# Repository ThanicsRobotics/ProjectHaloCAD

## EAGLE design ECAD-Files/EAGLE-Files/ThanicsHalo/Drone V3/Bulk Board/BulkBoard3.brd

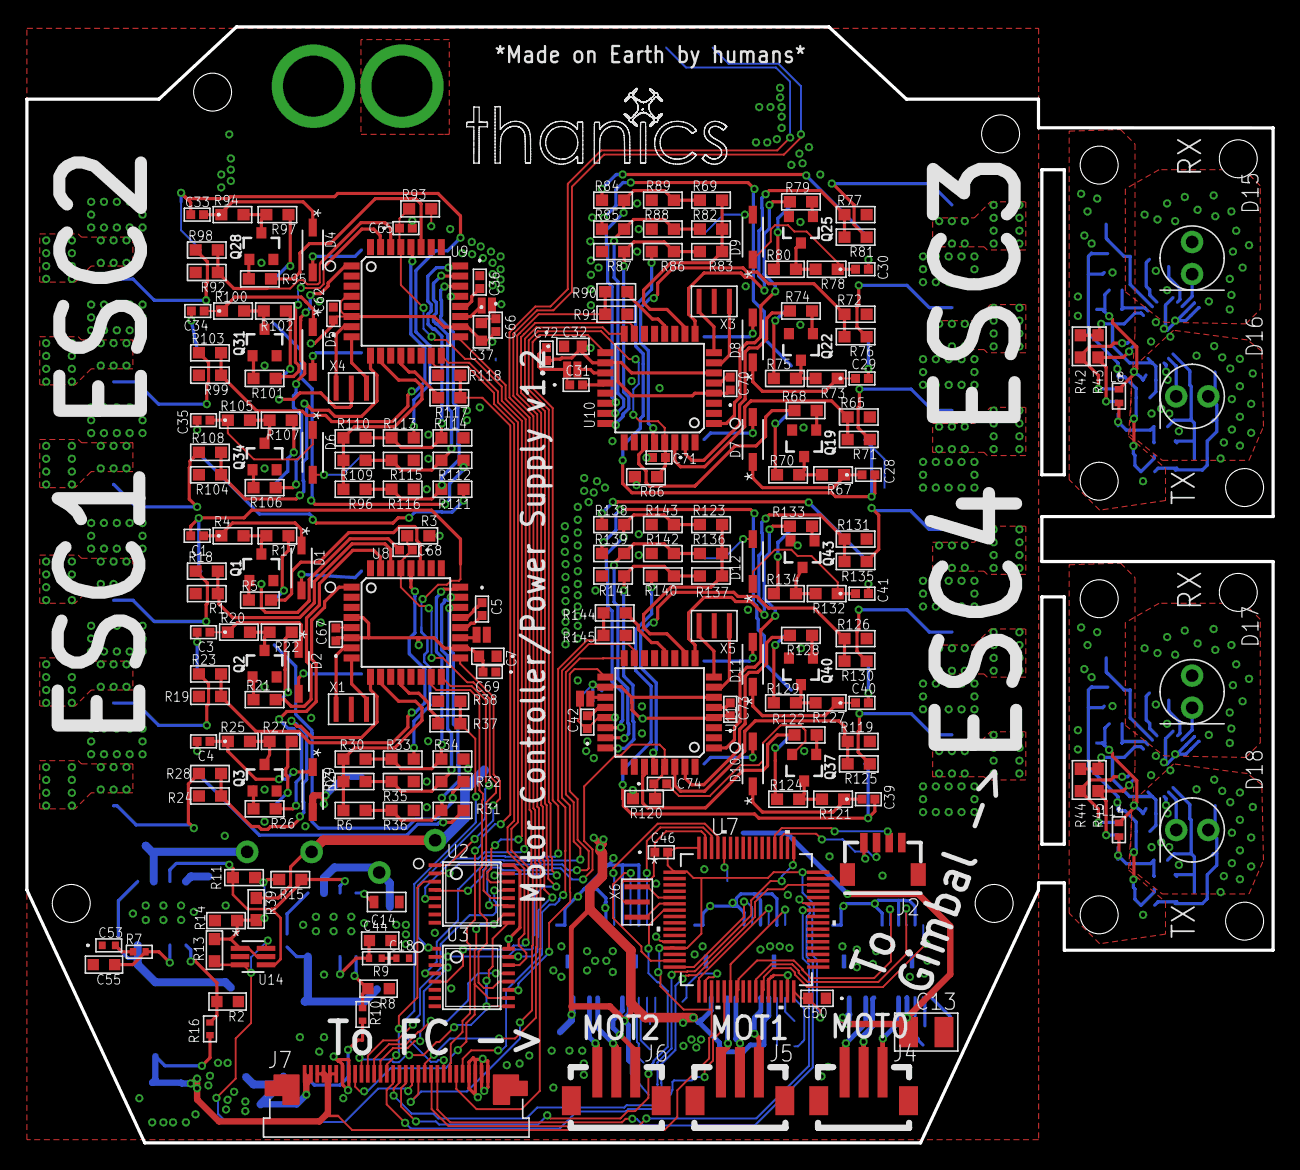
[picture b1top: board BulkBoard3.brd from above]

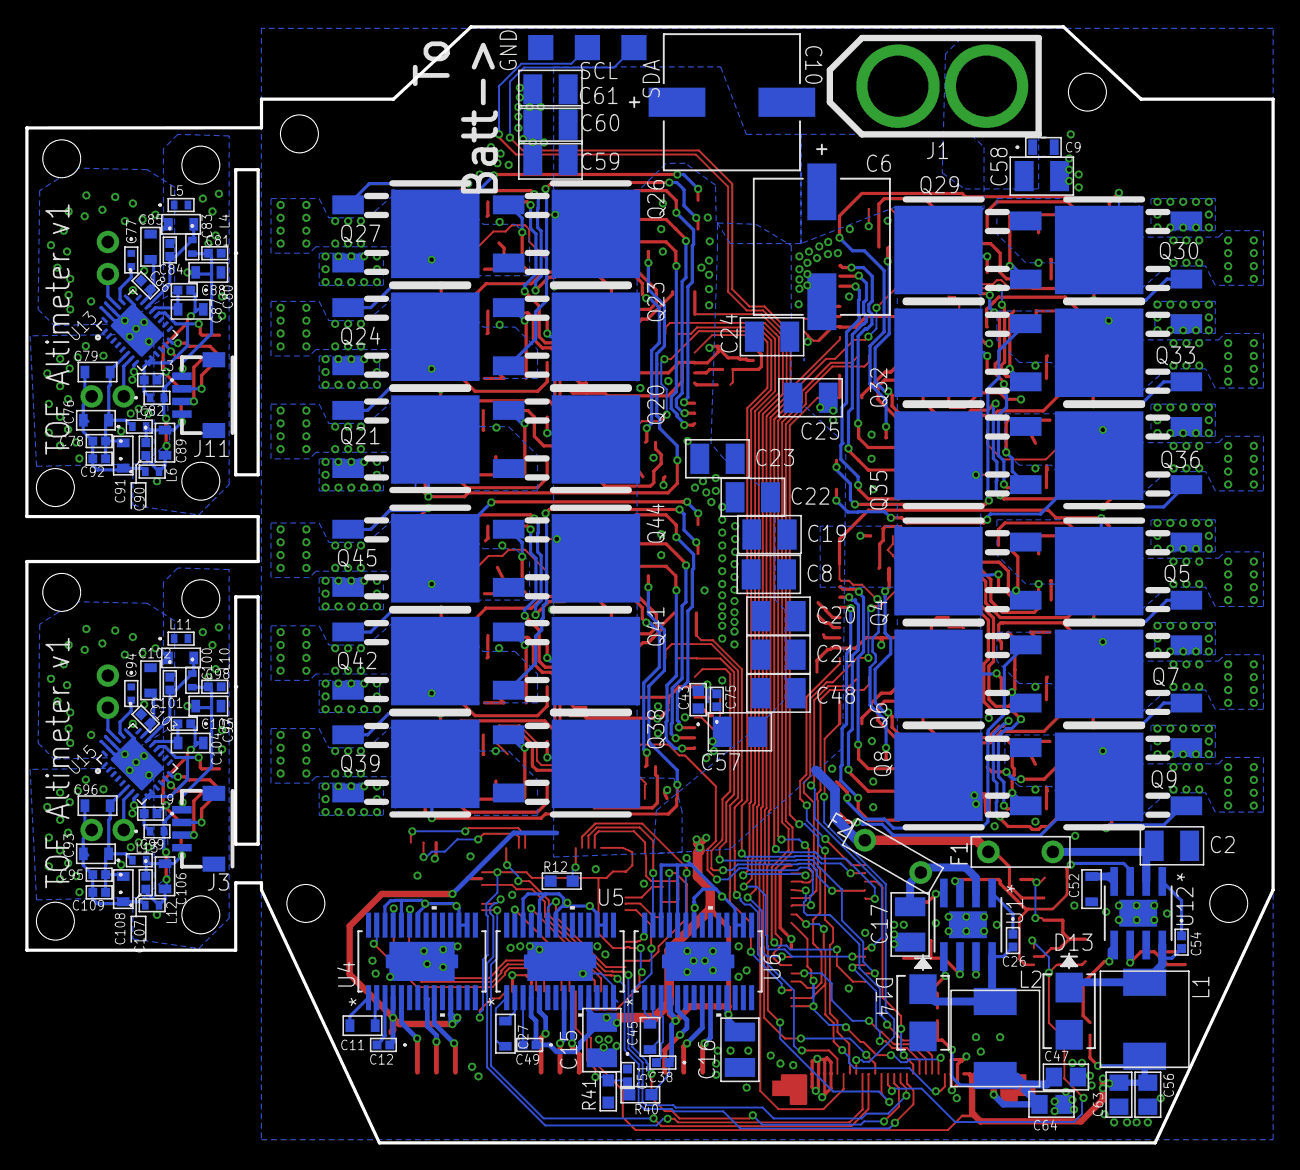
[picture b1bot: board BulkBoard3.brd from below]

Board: 4 copper layers, 98.6 x 88.3 mm, 340 parts (127 on the bottom side), 249 nets.

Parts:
C1, C3, C4, C28, C29, C30, C33, C34, C35, C39, C40, C41: 0.1uF (50V); 0402-M
C2, C8, C13, C15, C16, C17, C19, C20, C21, C22, C23, C24, C25, C48, C57, C58, C59, C60, C61: 22uF; 1210_CAPACITOR
C5, C12, C26, C31, C36, C38, C42, C46, C49, C51, C54, C62, C65, C66, C67, C68, C69, C70, C71, C72, C73, C74, C75, C78, C81, C82, C84, C86, C88, C90, C92, C95, C98, C99, C101, C103, C105, C107, C109: 0.1uF; 0402-M
C6, C10: 470uF; PCAP_10X10-ELECT-M
C7, C32, C37, C43, C50: 2.2uF; G-188-M
C9: 10uF; G-21
C11, C14, C27, C45, C52: 10nF; 0603_CAPACITOR
C18: 1nF; C0402
C44, C55: 43pF; C0603
C47, C56, C63, C64: 22uF; C0805
C53: 2.2nF; 0402_CAPACITOR
C76, C79, C80, C83, C85, C87, C89, C91, C93, C96, C97, C100, C102, C104, C106, C108: 1uF; 0603_CAPACITOR
C77, C94: 6pF; 0402_CAPACITOR
D1, D2, D3, D4, D5, D6, D7, D8, D9, D10, D11, D12: 1N4148; SOD123-M
D13, D14: SSB44-E3/52T; DIODE_DO214AA_MBRS-M
D15, D17: SFH203FA; 5MM_LED
D16, D18: SFH4550; 5MM_LED
F1, F2: 0ZRB0400FF1A
GND: TPTP20SQ; TP20SQ
J1: ESC_CONTACTS; XT60_CONNECTOR
J2, J3, J11: JST_SH_4POS
J4, J5, J6: B3B-ZR-SM4
J7: SFV30R-1STE1HLF
JP1, JP3, JP4, JP5: JUMPER-SMT_2_NO_NO-SILK; SMT-JUMPER_2_NO_NO-SILK
L1, L2: 10uH; PA431.XXX
L3, L4, L5, L6, L7, L8, L9, L10, L11, L12, L13, L14: MMZ1005S182ET000IND_1005-M; IND_1005-M
Q1, Q2, Q3, Q19, Q22, Q25, Q28, Q31, Q34, Q37, Q40, Q43: 500mA/300V; SOT23-3
Q4, Q5, Q6, Q7, Q8, Q9, Q20, Q21, Q23, Q24, Q26, Q27, Q29, Q30, Q32, Q33, Q35, Q36, Q38, Q39, Q41, Q42, Q44, Q45: IRLR8726; DPAK
R1, R3, R12, R19, R24, R37, R38, R40, R65, R66, R72, R77, R90, R91, R92, R93, R99, R104, R117, R118, R119, R120, R126, R131, R144, R145: 10k; RC0603N-M
R2: 3.24k; R0603
R4, R20, R25, R39, R67, R73, R78, R94, R100, R105, R121, R127, R132: 2.2k; RC0603N-M
R5, R21, R26, R34, R35, R36, R68, R74, R79, R87, R88, R89, R95, R101, R106, R114, R115, R116, R122, R128, R133, R141, R142, R143: 4.7k; RC0603N-M
R6, R29, R30, R31, R32, R33, R69, R82, R83, R84, R85, R86, R96, R109, R110, R111, R112, R113, R123, R136, R137, R138, R139, R140: 47k; RC0603N-M
R7: 28.7k; R0402
R8: 1.96k; R0603
R9: 39.2k; R0402
R10, R16: 10.2k; R0402
R11, R13, R15: 100k; RC0603N-M
R14, R42, R43, R44, R45: 1k; RC0603N-M
R17, R18, R22, R23, R27, R28, R70, R71, R75, R76, R80, R81, R97, R98, R102, R103, R107, R108, R124, R125, R129, R130, R134, R135: 100R; RC0603N-M
R41: 1.5k; RC0603N-M
SCL: TPTP20SQ; TP20SQ
SDA: TPTP20SQ; TP20SQ
U1, U12: TPS54331DRD8-M; D8-M
U2, U3: 74HC4052PW; TSSOP16
U4, U5, U6: DRV8313; PWP28_5P18X3P1-M
U7: STM32F103RCT6LQFP-64-M; LQFP-64-M
U8, U9, U10, U11: MEGA8-AI; TQFP32-08
U13, U15: OPT3101; 28-VQFN
U14: SN74LVC1G373DCKRDCK6-M; DCK6-M
X1, X3, X4, X5: 16MHz; 3-SMD
X6: 8MHz; 3-SMD

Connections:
+3V1: C80.1, C81.2, C89.1, C90.2, J11.1, L3.2, L4.2, L6.2
+3V2: C87.1, C88.2, U13.19
+3V3: C46.2, C50.2, C56.1, C63.1, J7.3, J7.4, J7.5, J7.6, L1.P$2, R16.2, U7.1, U7.13, U7.19, U7.32, U7.48, U7.64
+3V4: C97.1, C98.2, C106.1, C107.2, J3.1, L9.2, L10.2, L12.2
+3V5: C104.1, C105.2, U15.19
+5V: C7.2, C32.2, C37.2, C43.2, C47.1, C62.1, C64.1, C66.2, C67.1, C69.2, C70.1, C72.2, C73.1, C75.2, J2.4, J7.1, J7.2, L2.P$2, R3.2, R10.2, R66.2, R93.2, R120.2, U2.16, U3.16, U4.16, U4.17, U4.22, U4.24, U4.26, U5.16, U5.17, U5.22, U5.24, U5.26, U6.16, U6.17, U6.22, U6.24, U6.26, U8.4, U8.6, U8.18, U9.4, U9.6, U9.18, U10.4, U10.6, U10.18, U11.4, U11.6, U11.18
A0: U4.27, U7.27
A1: U5.27, U7.22
A2: U6.27, U7.62
AGND: C77.1, C83.2, C84.1, C85.2, C86.1, D15.A, L5.1, U13.23, U13.26, U13.27, U13.29
AGND1: C94.1, C100.2, C101.1, C102.2, C103.1, D17.A, L11.1, U15.23, U15.26, U15.27, U15.29
AHIN: R5.2, U8.27
AHIN2: R95.2, U9.27
AHIN3: R68.2, U10.27
AHIN4: R122.2, U11.27
ALIN: R1.1, R18.2, U8.30
ALIN2: R92.1, R98.2, U9.30
ALIN3: R65.1, R71.2, U10.30
ALIN4: R119.1, R125.2, U11.30
AOUT: C1.2, Q4.3, Q5.2, R33.1
AOUT2: C33.2, Q29.3, Q30.2, R113.1
AOUT3: C28.2, Q20.3, Q21.2, R86.1
AOUT4: C39.2, Q38.3, Q39.2, R140.1
AVCC: C83.1, C84.2, L4.1, U13.20
AVCC1: C100.1, C101.2, L10.1, U15.20
A_SENSE: R30.1, R33.2, R34.1, U8.24
A_SENSE2: R110.1, R113.2, R114.1, U9.24
A_SENSE3: R83.1, R86.2, R87.1, U10.24
A_SENSE4: R137.1, R140.2, R141.1, U11.24
B0: U4.25, U7.26
B1: U5.25, U7.17
B2: U6.25, U7.15
BATT_SCL: J7.20, SCL.TP
BATT_SDA: J7.19, SDA.TP
BHIN: R21.2, U8.31
BHIN2: R101.2, U9.31
BHIN3: R74.2, U10.31
BHIN4: R128.2, U11.31
BLIN: R19.1, R23.2, U8.28
BLIN2: R99.1, R103.2, U9.28
BLIN3: R72.1, R76.2, U10.28
BLIN4: R126.1, R130.2, U11.28
BOOT0: R12.2, U7.60
BOUT: C3.2, Q6.3, Q7.2, R32.1
BOUT2: C34.2, Q32.3, Q33.2, R112.1
BOUT3: C29.2, Q23.3, Q24.2, R85.1
BOUT4: C40.2, Q41.3, Q42.2, R139.1
B_SENSE: R29.1, R32.2, R35.1, U8.23
B_SENSE2: R109.1, R112.2, R115.1, U9.23
B_SENSE3: R82.1, R85.2, R88.1, U10.23
B_SENSE4: R136.1, R139.2, R142.1, U11.23
C0: U4.23, U7.23
C1: U5.23, U7.16
C2: U6.23, U7.61
CHIN: R26.2, U8.1
CHIN2: R106.2, U9.1
CHIN3: R79.2, U10.1
CHIN4: R133.2, U11.1
CLIN: R24.1, R28.2, U8.9
CLIN2: R104.1, R108.2, U9.9
CLIN3: R77.1, R81.2, U10.9
CLIN4: R131.1, R135.2, U11.9
COUT: C4.2, Q8.3, Q9.2, R31.1
COUT2: C35.2, Q35.3, Q36.2, R111.1
COUT3: C30.2, Q26.3, Q27.2, R84.1
COUT4: C41.2, Q44.3, Q45.2, R138.1
C_SENSE: R6.1, R31.2, R36.1, U8.22
C_SENSE2: R96.1, R111.2, R116.1, U9.22
C_SENSE3: R69.1, R84.2, R89.1, U10.22
C_SENSE4: R123.1, R138.2, R143.1, U11.22
EN: R11.2, R15.1, U1.3, U12.3, U14.4
GND: C2.2, C5.1, C6.2, C7.1, C8.1, C9.2, C10.2, C13.1, C14.1, C15.1, C16.1, C17.2, C18.2, C19.1, C20.1, C21.1, C22.1, C23.1, C24.1, C25.1, C31.1, C32.1, C36.1, C37.1, C42.1, C43.1, C44.2, C46.1, C47.2, C48.2, C50.1, C51.1, C52.1, C53.1, C55.2, C56.2, C57.2, C58.2, C59.2, C60.2, C61.2, C62.2, C63.2, C64.2, C65.2, C66.1, C67.2, C68.2, C69.1, C70.2, C71.2, C72.1, C73.2, C74.2, C75.1, D13.2, D14.2, GND.TP, J1.-, J2.1, J7.7, J7.8, J7.27, J7.28, J7.29, J7.30, JP1.2, JP3.2, JP4.2, JP5.2, Q1.2, Q2.2, Q3.2, Q5.3, Q7.3, Q9.3, Q19.2, Q21.3, Q22.2, Q24.3, Q25.2, Q27.3, Q28.2, Q30.3, Q31.2, Q33.3, Q34.2, Q36.3, Q37.2, Q39.3, Q40.2, Q42.3, Q43.2, Q45.3, R1.2, R2.1, R8.1, R12.1, R14.2, R19.2, R24.2, R34.2, R35.2, R36.2, R38.2, R41.2, R65.2, R72.2, R77.2, R87.2, R88.2, R89.2, R91.2, R92.2, R99.2, R104.2, R114.2, R115.2, R116.2, R118.2, R119.2, R126.2, R131.2, R141.2, R142.2, R143.2, R145.2, U1.7, U1.EP, U2.6, U2.7, U2.8, U3.6, U3.7, U3.8, U4.6, U4.7, U4.10, U4.14, U4.20, U4.28, U4.29, U5.6, U5.7, U5.10, U5.14, U5.20, U5.28, U5.29, U6.6, U6.7, U6.10, U6.14, U6.20, U6.28, U6.29, U7.12, U7.18, U7.28, U7.31, U7.47, U7.63, U8.3, U8.5, U8.21, U9.3, U9.5, U9.21, U10.3, U10.5, U10.21, U11.3, U11.5, U11.21, U12.7, U12.EP, U14.2, X1.2, X3.2, X4.2, X5.2, X6.2
GND1: C80.2, C81.1, C89.2, C90.1, J11.4, J11.P$5, J11.P$6, L5.2, L7.2, L8.2
GND2: C97.2, C98.1, C106.2, C107.1, J3.4, J3.P$5, J3.P$6, L11.2, L13.2, L14.2
GNDIO: C82.1, C87.2, C88.1, L8.1, U13.3, U13.4, U13.5, U13.8
GNDIO1: C99.1, C104.2, C105.1, L14.1, U15.3, U15.4, U15.5, U15.8
I2C_SCL: J11.3, R43.2, U13.13
I2C_SCL1: J3.3, R45.2, U15.13
I2C_SDA: J11.2, R42.2, U13.14
I2C_SDA1: J3.2, R44.2, U15.14
LIPO: C51.2, R40.2, R41.1, U7.21
MISO: J7.13, U3.3
MISO1: U3.1, U8.16
MISO2: U3.5, U9.16
MISO3: U3.2, U10.16
MISO4: U3.4, U11.16
MOSI: J7.12, U3.13
MOSI1: U3.12, U8.15
MOSI2: U3.14, U9.15
MOSI3: U3.15, U10.15
MOSI4: U3.11, U11.15
MOT0_1: J4.1, U4.5
MOT0_2: J4.2, U4.8
MOT0_3: J4.3, U4.9
MOT1_1: J5.1, U5.5
MOT1_2: J5.2, U5.8
MOT1_3: J5.3, U5.9
MOT2_1: J6.1, U6.5
MOT2_2: J6.2, U6.8
MOT2_3: J6.3, U6.9
unnamed: C11.1, U4.2
unnamed: C55.1, R7.2, U12.6
unnamed: C53.2, R7.1
unnamed: Q1.1, R5.1
unnamed: Q4.1, R17.1
unnamed: Q1.3, R4.2, R17.2
unnamed: Q2.1, R21.1
unnamed: C1.1, D1.C, R4.1
unnamed: Q5.1, R18.1
unnamed: Q6.1, R22.1
unnamed: C52.2, U12.4
unnamed: C54.1, U12.1
unnamed: C44.1, R9.2, U1.6
unnamed: C18.1, R9.1
unnamed: C14.2, U1.4
unnamed: C26.1, U1.1
unnamed: C26.2, D14.1, L2.P$1, U1.8
unnamed: C54.2, D13.1, L1.P$1, U12.8
unnamed: R8.2, R10.1, U1.5
unnamed: R2.2, R16.1, U12.5
unnamed: Q2.3, R20.2, R22.2
unnamed: C3.1, D2.C, R20.1
unnamed: D16.C, U13.7
unnamed: Q7.1, R23.1
unnamed: Q3.1, R26.1
unnamed: C77.2, U13.24
unnamed: D15.C, U13.25
unnamed: C85.1, C86.2, U13.21
unnamed: D18.C, U15.7
unnamed: Q8.1, R27.1
unnamed: Q3.3, R25.2, R27.2
unnamed: C4.1, D3.C, R25.1
unnamed: Q9.1, R28.1
unnamed: C5.2, U8.20
unnamed: U8.7, X1.3
unnamed: U8.8, X1.1
unnamed: C11.2, U4.1
unnamed: JP1.1, U8.19
unnamed: C27.1, U5.2
unnamed: C27.2, U5.1
unnamed: C49.2, U5.3
unnamed: C45.1, U6.2
unnamed: C45.2, U6.1
unnamed: R37.2, U8.12
unnamed: C38.2, U6.3
unnamed: U7.5, X6.3
unnamed: C12.2, U4.3
unnamed: U7.6, X6.1
unnamed: C94.2, U15.24
unnamed: D17.C, U15.25
unnamed: C102.1, C103.2, U15.21
unnamed: Q19.1, R68.1
unnamed: Q20.1, R70.1
unnamed: Q19.3, R67.2, R70.2
unnamed: C28.1, D7.C, R67.1
unnamed: Q21.1, R71.1
unnamed: Q22.1, R74.1
unnamed: Q23.1, R75.1
unnamed: Q22.3, R73.2, R75.2
unnamed: C29.1, D8.C, R73.1
unnamed: Q24.1, R76.1
unnamed: Q25.1, R79.1
unnamed: Q26.1, R80.1
unnamed: Q25.3, R78.2, R80.2
unnamed: C30.1, D9.C, R78.1
unnamed: Q27.1, R81.1
unnamed: R90.2, U10.12
unnamed: JP3.1, U10.19
unnamed: C31.2, U10.20
unnamed: U10.7, X3.3
unnamed: U10.8, X3.1
unnamed: Q28.1, R95.1
unnamed: Q29.1, R97.1
unnamed: Q28.3, R94.2, R97.2
unnamed: C33.1, D4.C, R94.1
unnamed: Q30.1, R98.1
unnamed: Q31.1, R101.1
unnamed: Q32.1, R102.1
unnamed: Q31.3, R100.2, R102.2
unnamed: C34.1, D5.C, R100.1
unnamed: Q33.1, R103.1
unnamed: Q34.1, R106.1
unnamed: Q35.1, R107.1
unnamed: Q34.3, R105.2, R107.2
unnamed: C35.1, D6.C, R105.1
unnamed: Q36.1, R108.1
unnamed: R117.2, U9.12
unnamed: JP4.1, U9.19
unnamed: C36.2, U9.20
unnamed: U9.7, X4.3
unnamed: U9.8, X4.1
unnamed: Q37.1, R122.1
unnamed: Q38.1, R124.1
unnamed: Q37.3, R121.2, R124.2
unnamed: C39.1, D10.C, R121.1
unnamed: Q39.1, R125.1
unnamed: Q40.1, R128.1
unnamed: Q41.1, R129.1
unnamed: Q40.3, R127.2, R129.2
unnamed: C40.1, D11.C, R127.1
unnamed: Q42.1, R130.1
unnamed: Q43.1, R133.1
unnamed: Q44.1, R134.1
unnamed: Q43.3, R132.2, R134.2
unnamed: C41.1, D12.C, R132.1
unnamed: Q45.1, R135.1
unnamed: R144.2, U11.12
unnamed: JP5.1, U11.19
unnamed: C42.2, U11.20
unnamed: U11.7, X5.3
unnamed: U11.8, X5.1
NEUTRAL_SENSE: R6.2, R29.2, R30.2, U8.10
NEUTRAL_SENSE2: R96.2, R109.2, R110.2, U9.10
NEUTRAL_SENSE3: R69.2, R82.2, R83.2, U10.10
NEUTRAL_SENSE4: R123.2, R136.2, R137.2, U11.10
NT-RX: J2.2, U7.52
NT-TX: J2.3, U7.51
PWM: J7.23, R37.1, R38.1
PWM2: J7.24, R117.1, R118.1
PWM3: J7.25, R90.1, R91.1
PWM4: J7.26, R144.1, R145.1
PWR_EN: J7.18, R13.2, U14.3, U14.6
RESET: J7.17, U7.7
RST: J7.11, U2.13
RST1: C68.1, R3.1, U2.12, U8.29
RST2: C65.1, R93.1, U2.14, U9.29
RST3: C71.1, R66.1, U2.15, U10.29
RST4: C74.1, R120.1, U2.11, U11.29
RX: J7.22, U7.43
SCK: J7.14, U2.3
SCK1: U2.1, U8.17
SCK2: U2.5, U9.17
SCK3: U2.2, U10.17
SCK4: U2.4, U11.17
SEL0: J7.9, U2.10, U3.10
SEL1: J7.10, U2.9, U3.9
SWCLK: J7.16, U7.49
SWDIO: J7.15, U7.46
TX: J7.21, U7.42
V2FUSED: C17.1, F2.2, U1.2
VCCIO: C82.2, L3.1, R42.1, R43.1, U13.9, U13.10, U13.18
VCCIO1: C99.2, L9.1, R44.1, R45.1, U15.9, U15.10, U15.18
VDD: C6.1, C8.2, C9.1, C10.1, C12.1, C13.2, C15.2, C16.2, C19.2, C20.2, C21.2, C22.2, C23.2, C24.2, C25.2, C38.1, C48.1, C49.1, C57.1, C58.1, C59.1, C60.1, C61.1, D1.A, D2.A, D3.A, D4.A, D5.A, D6.A, D7.A, D8.A, D9.A, D10.A, D11.A, D12.A, F1.1, F2.1, J1.+, Q4.2, Q6.2, Q8.2, Q20.2, Q23.2, Q26.2, Q29.2, Q32.2, Q35.2, Q38.2, Q41.2, Q44.2, R39.1, R40.1, U4.4, U4.11, U5.4, U5.11, U6.4, U6.11
VDDLED: C76.2, C78.2, C79.2, C91.1, C92.2, D16.A, L6.1
VDDLED1: C93.2, C95.2, C96.2, C108.1, C109.2, D18.A, L12.1
VFUSED: C2.1, F1.2, U12.2
VSS: C76.1, C78.1, C79.1, C91.2, C92.1, L7.1, U13.6
VSS1: C93.1, C95.1, C96.1, C108.2, C109.1, L13.1, U15.6
V_LATCH: R11.1, R13.1, R14.1, R15.2, R39.2, U14.1, U14.5

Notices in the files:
parts and their libraries:
SparkFun-DiscreteSemi: Licensing: Creative Commons ShareAlike 4.0 International - https://creativecommons.org/licenses/by-sa/4.0
COPYRIGHT: Copyright C 2015 Accelerated Designs. All rights reserved
